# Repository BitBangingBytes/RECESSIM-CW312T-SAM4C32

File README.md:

Target board as seen in [RECESSIM video](https://www.youtube.com/watch?v=IOD5voFTAz8)

Rev2 of this board, the TX/RX UART pins have been fixed.

Gerbers generated and available in Rev2 zip file, but have not been sent to board house and tested. DRC Passed.

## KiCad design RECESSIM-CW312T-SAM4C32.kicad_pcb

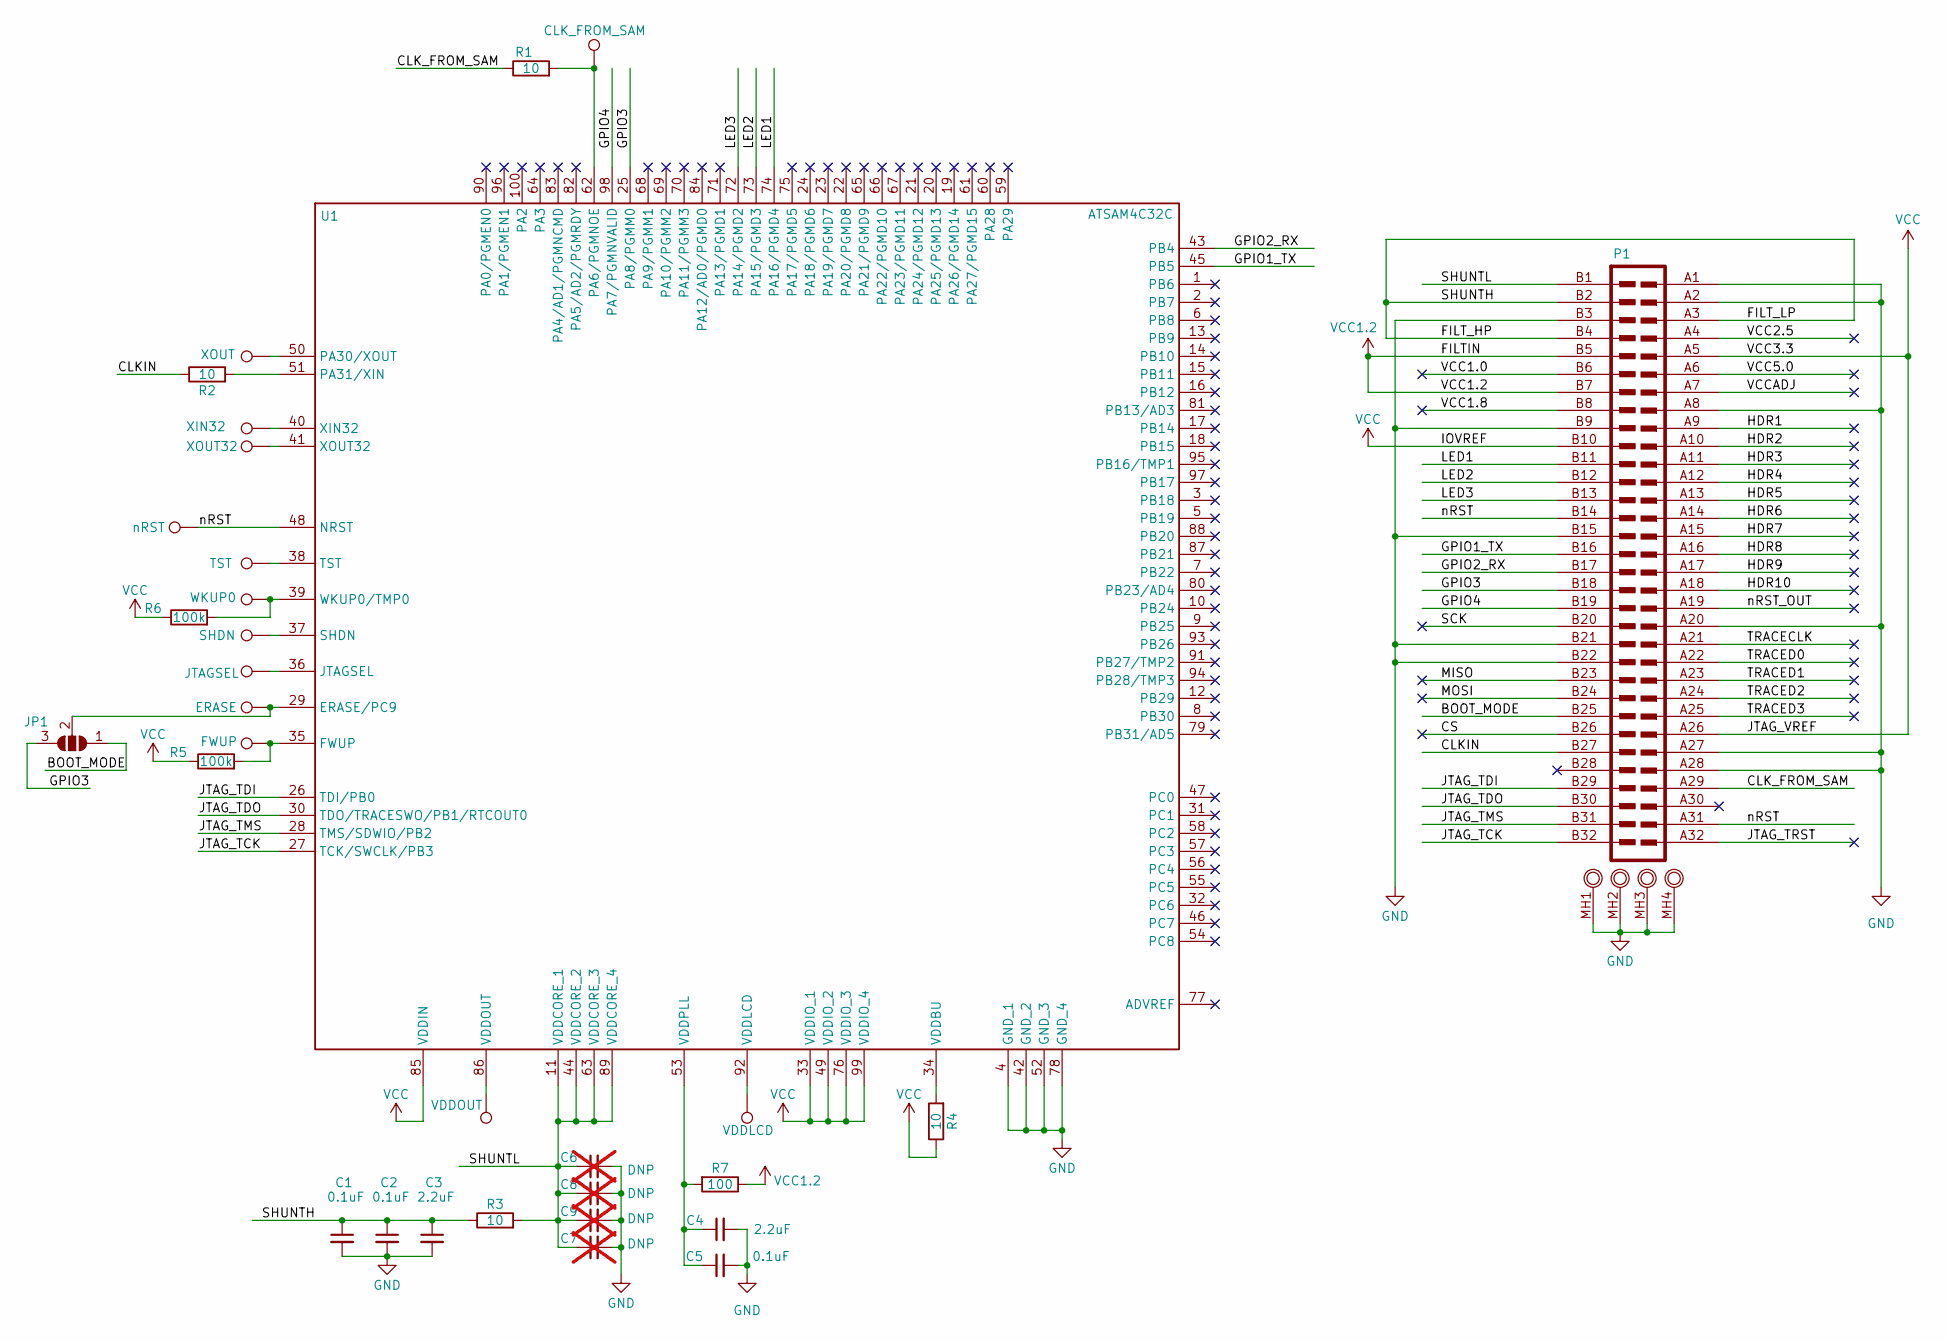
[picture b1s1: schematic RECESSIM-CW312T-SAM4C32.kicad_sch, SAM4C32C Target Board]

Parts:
C1, C2, C5: 0.1uF; C_0603_1608Metric
C3, C4: 2.2uF; C_0603_1608Metric
C6, C7, C8, C9: DNP; C_0603_1608Metric; not fitted
JP1: SolderJumper_3_Open; SolderJumper-3_P1.3mm_Open_RoundedPad1.0x1.5mm
P1: CW312_CardEdge
R1, R2, R3, R4: 10; R_0603_1608Metric
R5, R6: 100k; R_0603_1608Metric
R7: 100; R_0603_1608Metric
TP5: ERASE; TestPoint_Pad_1.0x1.0mm
TP6: FWUP; TestPoint_Pad_1.0x1.0mm
TP7: JTAGSEL; TestPoint_Pad_1.0x1.0mm
TP8: SHDN; TestPoint_Pad_1.0x1.0mm
TP9: VDDLCD; TestPoint_Pad_1.0x1.0mm
TP10: TST; TestPoint_Pad_1.0x1.0mm
TP11: VDDOUT; TestPoint_Pad_1.0x1.0mm
TP12: WKUP0; TestPoint_Pad_1.0x1.0mm
TP13: XIN32; TestPoint_Pad_1.0x1.0mm
TP14: XOUT32; TestPoint_Pad_1.0x1.0mm
TP15: nRST; TestPoint_Pad_1.0x1.0mm
TP16: XOUT; TestPoint_Pad_1.0x1.0mm
TP22: CLK_FROM_SAM; TestPoint_Pad_1.0x1.0mm
U1: ATSAM4C32C; TQFP-100_14x14mm_P0.5mm_W0.28mm

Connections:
/BOOT_MODE: JP1.1 (A), P1.B25
/CLKIN: P1.B27, R2.1
/CLK_FROM_SAM: P1.A29, R1.1
/CS: P1.B26
/FILT_HP: C1.1, C2.1, C3.1, P1.A3, P1.B2, P1.B4, R3.1
/GPIO1_TX: P1.B16, U1.45 (PB5)
/GPIO2_RX: P1.B17, U1.43 (PB4)
/GPIO3: JP1.3 (B), P1.B18, U1.25 (PA8/PGMM0)
/GPIO4: P1.B19, U1.98 (PA7/PGMNVALID)
/HDR1: P1.A9
/HDR2: P1.A10
/HDR3: P1.A11
/HDR4: P1.A12
/HDR5: P1.A13
/HDR6: P1.A14
/HDR7: P1.A15
/HDR8: P1.A16
/HDR9: P1.A17
/HDR10: P1.A18
/JTAG_TCK: P1.B32, U1.27 (TCK/SWCLK/PB3)
/JTAG_TDI: P1.B29, U1.26 (TDI/PB0)
/JTAG_TDO: P1.B30, U1.30 (TDO/TRACESWO/PB1/RTCOUT0)
/JTAG_TMS: P1.B31, U1.28 (TMS/SDWIO/PB2)
/JTAG_TRST: P1.A32
/LED1: P1.B11, U1.74 (PA16/PGMD4)
/LED2: P1.B12, U1.73 (PA15/PGMD3)
/LED3: P1.B13, U1.72 (PA14/PGMD2)
/MISO: P1.B23
/MOSI: P1.B24
/SCK: P1.B20
/SHUNTL: C6.1, C7.1, C8.1, C9.1, P1.B1, R3.2, U1.11 (VDDCORE_1), U1.44 (VDDCORE_2), U1.63 (VDDCORE_3), U1.89 (VDDCORE_4)
/TRACECLK: P1.A21
/TRACED0: P1.A22
/TRACED1: P1.A23
/TRACED2: P1.A24
/TRACED3: P1.A25
/VCC1.0: P1.B6
/VCC1.8: P1.B8
/VCC2.5: P1.A4
/VCC5.0: P1.A6
/VCCADJ: P1.A7
/nRST: P1.A31, P1.B14, TP15.1, U1.48 (NRST)
/nRST_OUT: P1.A19
GND: C1.2, C2.2, C3.2, C4.2, C5.2, C6.2, C7.2, C8.2, C9.2, P1.A1, P1.A2, P1.A8, P1.A20, P1.A27, P1.A28, P1.B3, P1.B9, P1.B15, P1.B21, P1.B22, P1.MH1 (MH), P1.MH2 (MH), P1.MH3 (MH), P1.MH4 (MH), U1.4 (GND_1), U1.42 (GND_2), U1.52 (GND_3), U1.78 (GND_4)
unnamed: JP1.2 (C), TP5.1, U1.29 (ERASE/PC9)
unnamed: R5.2, TP6.1, U1.35 (FWUP)
unnamed: TP7.1, U1.36 (JTAGSEL)
unnamed: R1.2, TP22.1, U1.62 (PA6/PGMNOE)
unnamed: TP16.1, U1.50 (PA30/XOUT)
unnamed: R2.2, U1.51 (PA31/XIN)
unnamed: TP8.1, U1.37 (SHDN)
unnamed: TP10.1, U1.38 (TST)
unnamed: R4.2, U1.34 (VDDBU)
unnamed: TP9.1, U1.92 (VDDLCD)
unnamed: TP11.1, U1.86 (VDDOUT)
unnamed: C4.1, C5.1, R7.2, U1.53 (VDDPLL)
unnamed: R6.2, TP12.1, U1.39 (WKUP0/TMP0)
unnamed: TP13.1, U1.40 (XIN32)
unnamed: TP14.1, U1.41 (XOUT32)
VCC: P1.A5, P1.A26, P1.B10, R4.1, R5.1, R6.1, U1.33 (VDDIO_1), U1.49 (VDDIO_2), U1.76 (VDDIO_3), U1.85 (VDDIN), U1.99 (VDDIO_4)
VCC1.2: P1.B5, P1.B7, R7.1

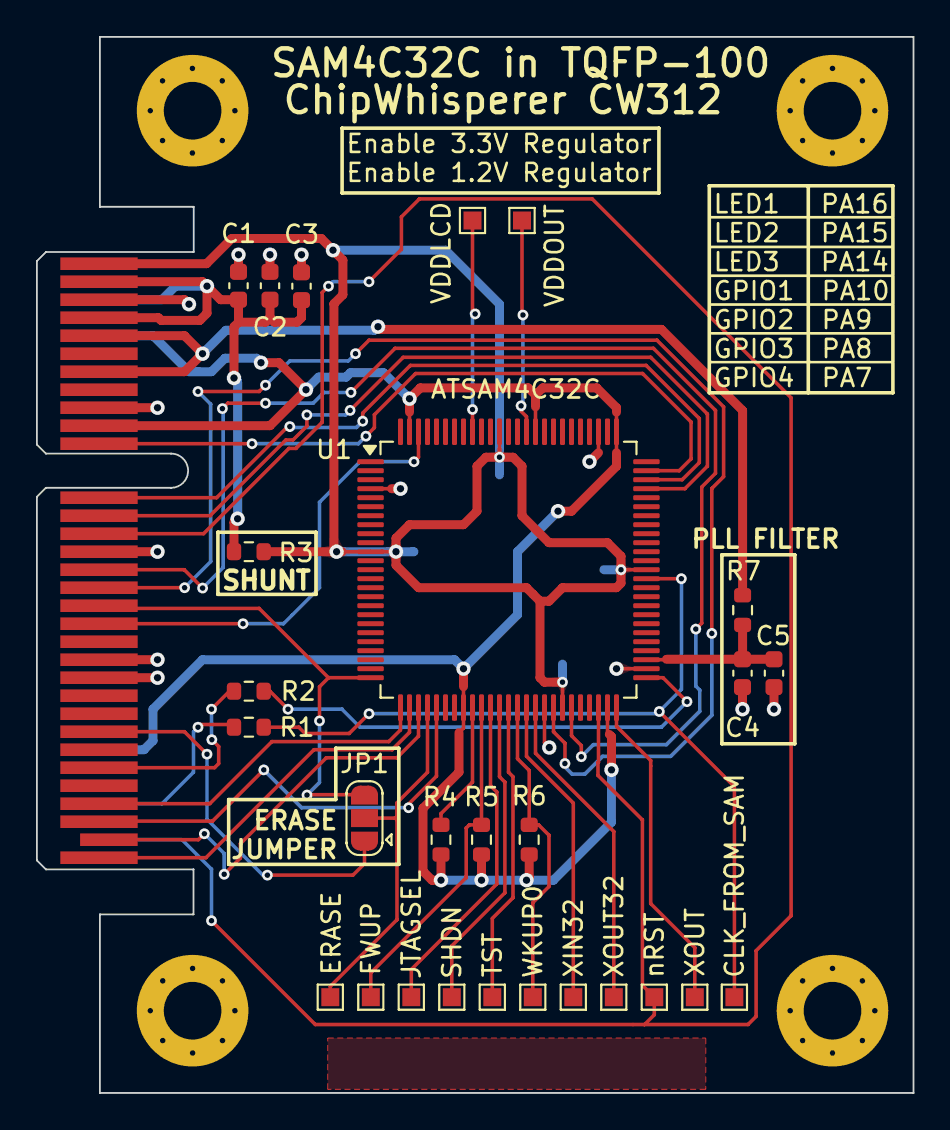
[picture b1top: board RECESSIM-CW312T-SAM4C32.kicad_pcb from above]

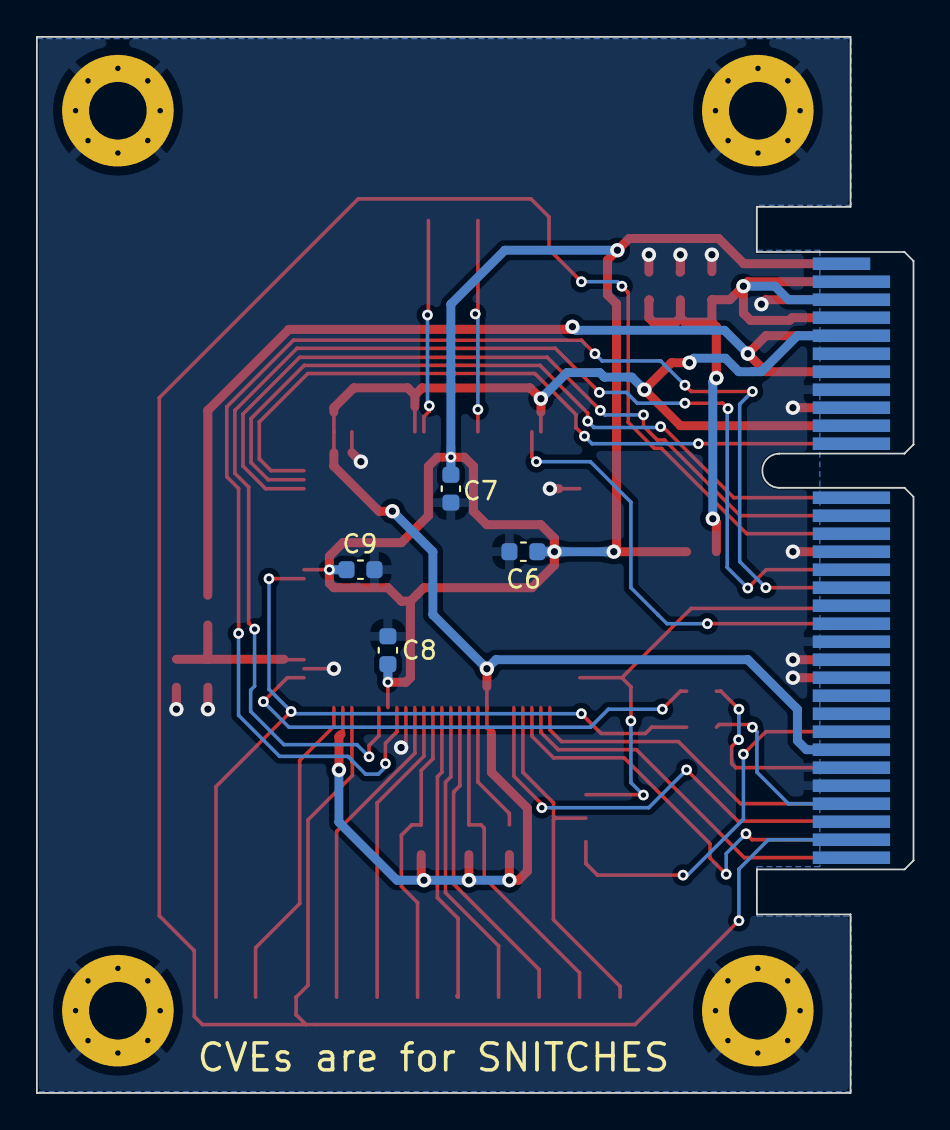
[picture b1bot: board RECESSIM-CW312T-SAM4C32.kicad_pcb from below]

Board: 2 copper layers, 48.7 x 58.7 mm, 32 parts (4 on the bottom side), 35 nets.

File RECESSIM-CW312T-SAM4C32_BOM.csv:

Reference,Value,Datasheet,Footprint,Qty,DNP,Digikey
"C1,C2,C5",0.1uF,~,Capacitor_SMD:C_0603_1608Metric,3,,478-KGM15AR70J104KMCT-ND
"C3,C4",2.2uF,~,Capacitor_SMD:C_0603_1608Metric,2,,1276-1886-1-ND
"C6,C7,C8,C9",0.1uF,~,Capacitor_SMD:C_0603_1608Metric,4,DNP,478-KGM15AR70J104KMCT-ND
"R1,R2,R3,R4",10,~,Resistor_SMD:R_0603_1608Metric,4,,RR08Q10DCT-ND
"R5,R6",100k,~,Resistor_SMD:R_0603_1608Metric,2,,RR08P100KDCT-ND
R7,100,~,Resistor_SMD:R_0603_1608Metric,1,,RR08P100DCT-ND
U1,ATSAM4C32C,,RECESSIM-CW312T-SAM4C32:TQFP-100_14x14mm_P0.5mm_W0.28mm,1,,150-ATSAM4C32CA-AUT-ND

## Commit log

2024-12-16 Added test points, power and JTAG connections
2024-12-16 Connected VDDBU to power, added more test points
2024-12-16 Added .gitignore to ignore backup files and directories
2024-12-16 Added more test points
2024-12-16 Added CW312T card edge footprint, finalized schematic before annotating
2024-12-16 Updated schematic footprint, annotated and ran DRC
2024-12-16 Updated footprints for card edge and initial placement of components on board
2024-12-17 Added two necessary resistors and removed one unnecessary one
2024-12-25 Finalized PCB design, generated gerbers for version 1
2024-12-27 Finalized Rev1 of the PCB design, removed unused Test Points from Schematic
2024-12-27 Changed processor footprint to have pad spacing of 0.22mm so black solder mask will bridge.
2025-01-01 Created BOM and added Digikey P/N's
2025-05-02 Fixed TX/RX being routed to wrong pins, updated PCB and regenerated gerbers
2025-05-02 Fixed TX/RX UART pin locations, updated PCB and regenerated gerbers
2025-05-02 Resolve merge conflict in KiCad project file
2025-05-02 Added Readme
